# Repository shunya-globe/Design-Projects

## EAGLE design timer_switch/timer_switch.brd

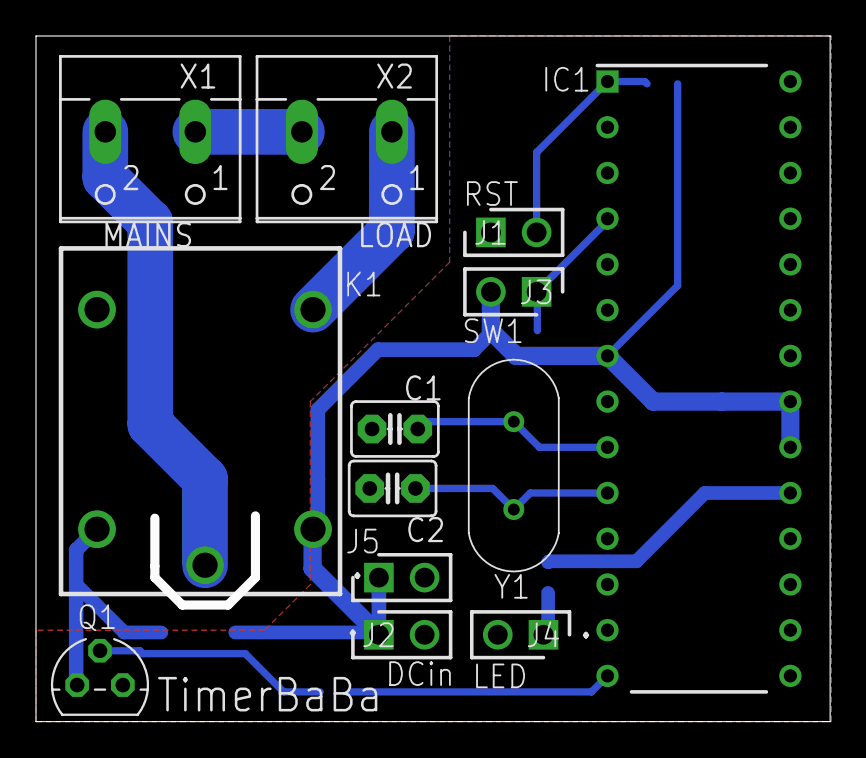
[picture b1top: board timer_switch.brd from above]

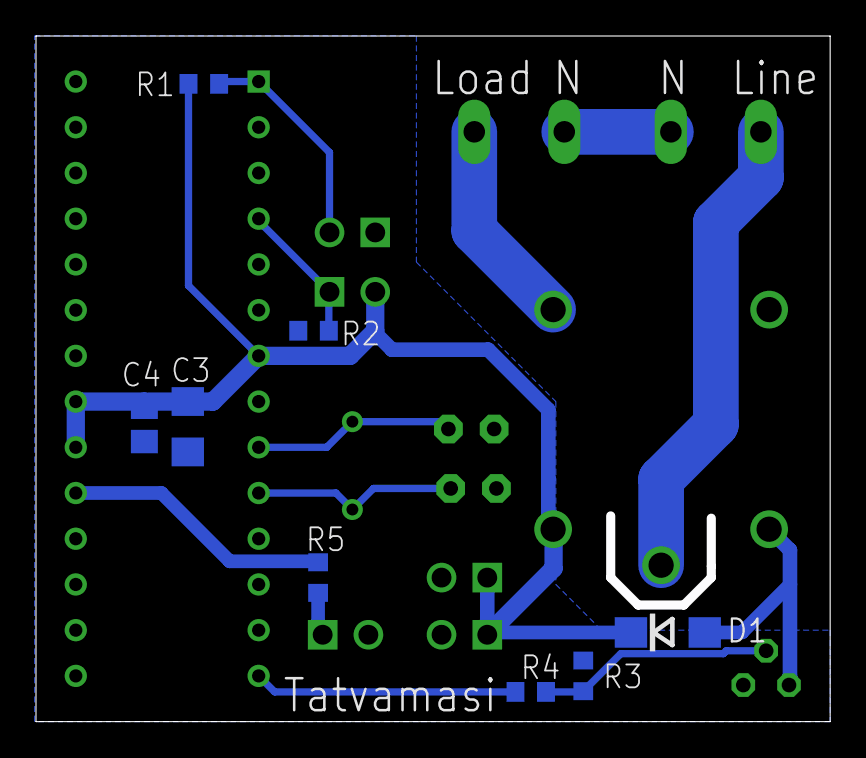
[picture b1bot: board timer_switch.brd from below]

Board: 2 copper layers, 44.1 x 38.1 mm, 21 parts (8 on the bottom side), 14 nets.

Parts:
C1, C2: 22pF; C2.5-3
C3: C1206
C4: C0805
D1: DO214AC
IC1: ATMEGA8L-8PU; DIP1016W53P254L3467H457Q28N
J1, J5: RST; HDRV2W64P0X254_1X2_508X254X864
J2: DCin; HDRV2W64P0X254_1X2_508X254X864
J3: SW1; HDRV2W64P0X254_1X2_508X254X864
J4: LED; HDRV2W64P0X254_1X2_508X254X864
K1: ORWH-SH-112D1F,000; ORWH-1T
Q1: BC547; TO92
R1, R2, R3: 10K; R0603
R4: 1K; R0603
R5: R0603
X1: MAINS; W237-102
X2: LOAD; W237-102
Y1: 16MHz; HC/49US_(AT49)PTH

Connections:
5V: C3.1, C4.1, D1.C, IC1.7, IC1.20, IC1.21, J2.1, J3.2, J5.1, K1.4, R1.2
D13: IC1.19, R5.2
GND: C1.2, C2.2, C3.2, C4.2, IC1.8, IC1.22, J1.1, J2.2, J4.2, J5.2, Q1.1, R2.2, R3.2
LOAD_LINE: K1.3, X1.2
MAINS_LINE: K1.5, X2.1
MAINS_NEU: X1.1, X2.2
unnamed: D1.A, K1.2, Q1.3
unnamed: Q1.2, R3.1, R4.2
unnamed: J4.1, R5.1
RELAY1: IC1.14, R4.1
SW1: IC1.4, J3.1, R2.1
X1: C1.1, IC1.9, Y1.2
X2: C2.1, IC1.10, Y1.1
~RESET: IC1.1, J1.2, R1.1

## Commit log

2019-02-07 update07feb2019
2019-02-11 Create TimerSwitch
2019-02-11 timer
2019-03-03 Create timer_switch.l##
